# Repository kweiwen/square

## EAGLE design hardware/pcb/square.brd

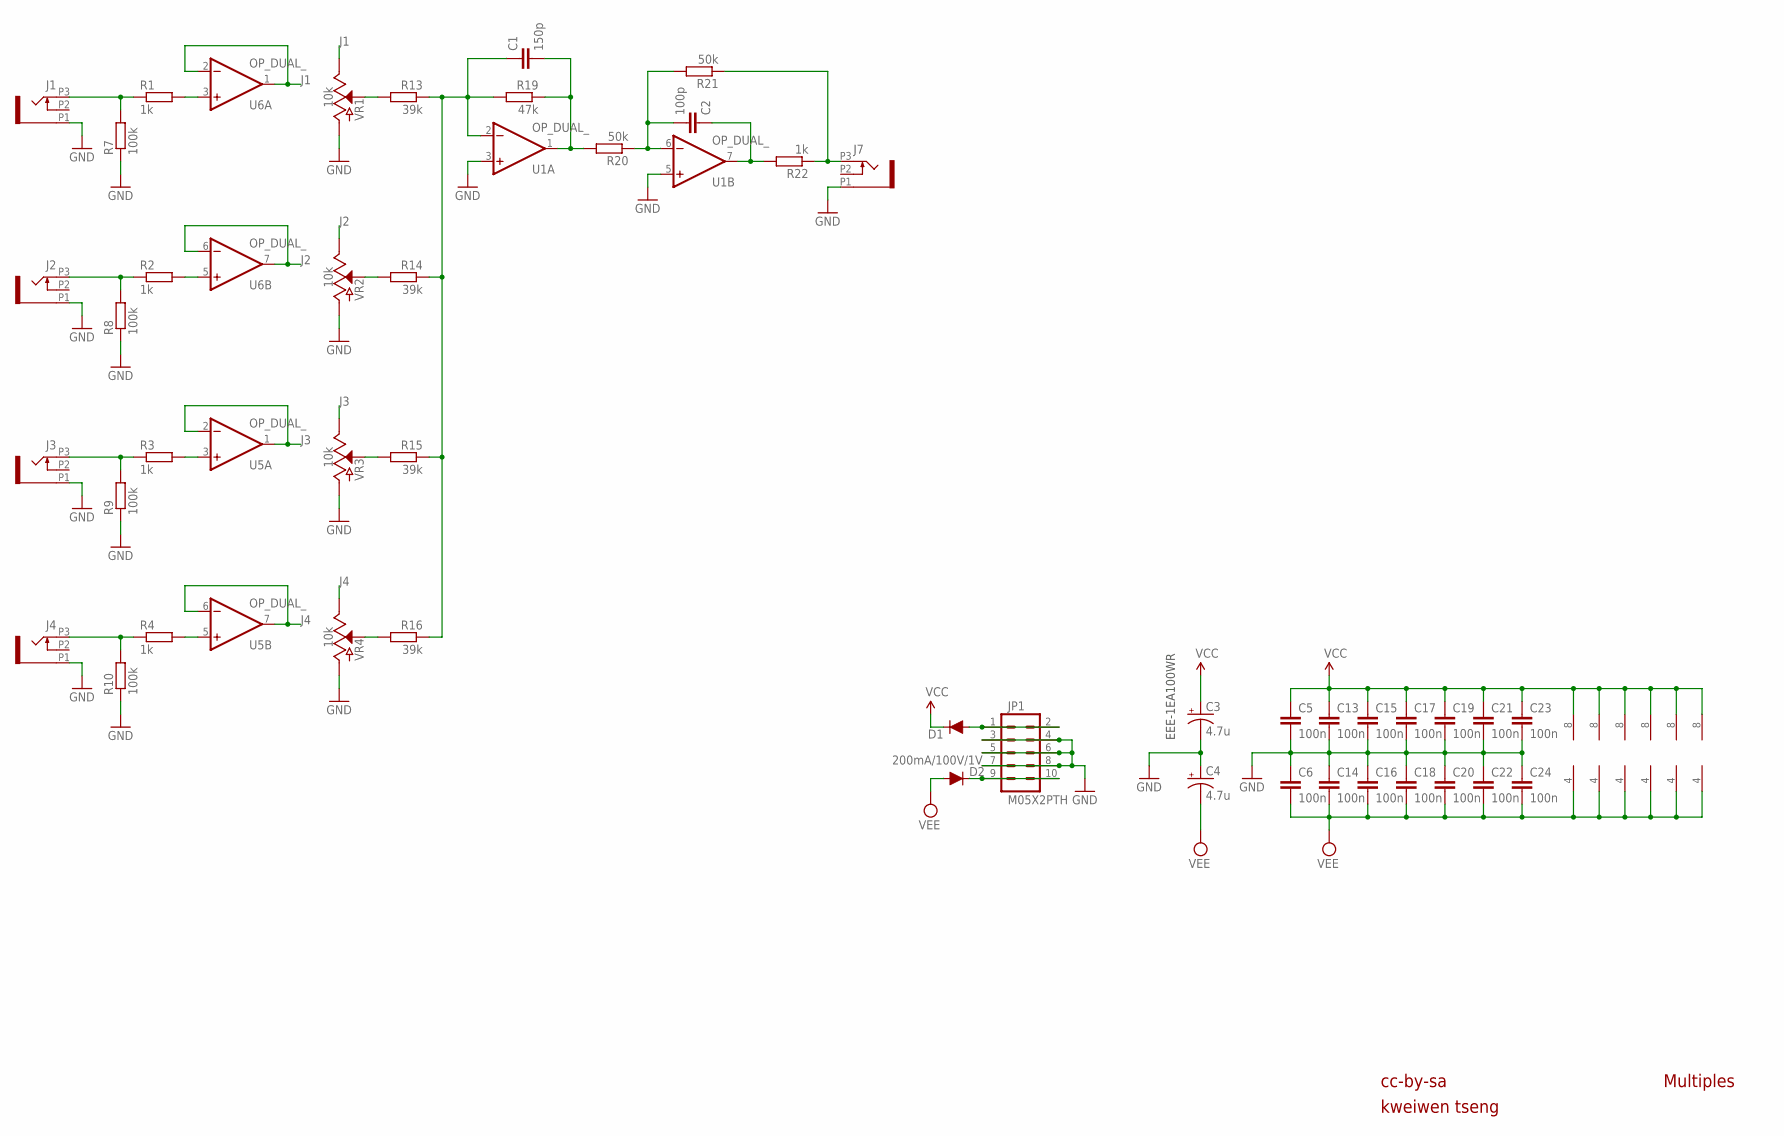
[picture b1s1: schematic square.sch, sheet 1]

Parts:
C1: 150p; C5B2.5
C2: 100p; C5B2.5
C3, C4: 4.7u; E2,5-6
C5, C6, C13, C14, C15, C16, C17, C18, C19, C20, C21, C22, C23, C24: 100n; C5B2.5
D1, D2: 200mA/100V/1V; DIODE-1N4148
J1, J2, J3, J4, J7: PJ301_THONKICONN6; WQP_PJ_301M6
JP1: M05X2PTH; AVR_ICSP
R1, R2, R3, R4, R22: 1k; VERTICAL_RESISTOR
R7, R8, R9, R10: 100k; VERTICAL_RESISTOR
R13, R14, R15, R16: 39k; VERTICAL_RESISTOR
R19: 47k; VERTICAL_RESISTOR
R20, R21: 50k; VERTICAL_RESISTOR
U1, U2, U3, U4, U5, U6: OP_DUAL_; DIL08
VR1, VR2, VR3, VR4: 10k; POT-PTH-ALPS-KIT

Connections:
GND: C3.-, C4.+, C5.2, C6.1, J1.P1 (1), J2.P1 (1), J3.P1 (1), J4.P1 (1), J7.P1 (1), JP1.3, JP1.4, JP1.5, JP1.6, JP1.7, JP1.8, R7.1, R8.1, R9.1, R10.1, U1.3 (+IN), U1.5 (+IN), VR1.P$1 (A), VR2.P$1 (A), VR3.P$1 (A), VR4.P$1 (A); also elsewhere on the board
GND1: C13.2, C14.1
GND2: C15.2, C16.1
GND3: C17.2, C18.1
GND4: C19.2, C20.1
GND5: C21.2, C22.1
GND6: C23.2, C24.1
J1: U6.1 (OUT), U6.2 (-IN), VR1.P$3 (E); also elsewhere on the board
J2: U6.6 (-IN), U6.7 (OUT), VR2.P$3 (E); also elsewhere on the board
J3: U5.1 (OUT), U5.2 (-IN), VR3.P$3 (E); also elsewhere on the board
J4: U5.6 (-IN), U5.7 (OUT), VR4.P$3 (E); also elsewhere on the board
unnamed: C1.1, R13.1, R14.1, R15.1, R16.1, R19.2, U1.2 (-IN)
unnamed: R13.2, VR1.P$2 (S)
unnamed: R16.2, VR4.P$2 (S)
unnamed: R1.2, U6.3 (+IN)
unnamed: R14.2, VR2.P$2 (S)
unnamed: D1.A, JP1.1, JP1.2
unnamed: R15.2, VR3.P$2 (S)
unnamed: C1.2, R19.1, R20.2, U1.1 (OUT)
unnamed: C2.2, R20.1, R21.2, U1.6 (-IN)
unnamed: C2.1, R22.2, U1.7 (OUT)
unnamed: J7.P3 (3), R21.1, R22.1
unnamed: R2.2, U6.5 (+IN)
unnamed: R3.2, U5.3 (+IN)
unnamed: D2.C, JP1.9, JP1.10
unnamed: J1.P3 (3), R1.1, R7.2
unnamed: J2.P3 (3), R2.1, R8.2
unnamed: J3.P3 (3), R3.1, R9.2
unnamed: J4.P3 (3), R4.1, R10.2
unnamed: R4.2, U5.5 (+IN)
VCC: C3.+, C5.1, C13.1, C15.1, C17.1, C19.1, C21.1, C23.1, D1.C, U1.8 (V+), U2.8 (V+), U3.8 (V+), U4.8 (V+), U5.8 (V+), U6.8 (V+)
VEE: C4.-, C6.2, C14.2, C16.2, C18.2, C20.2, C22.2, C24.2, D2.A, U1.4 (V-), U2.4 (V-), U3.4 (V-), U4.4 (V-), U5.4 (V-), U6.4 (V-)

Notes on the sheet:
cc-by-sa
kweiwen tseng
Multiples
EEE-1EA100WR

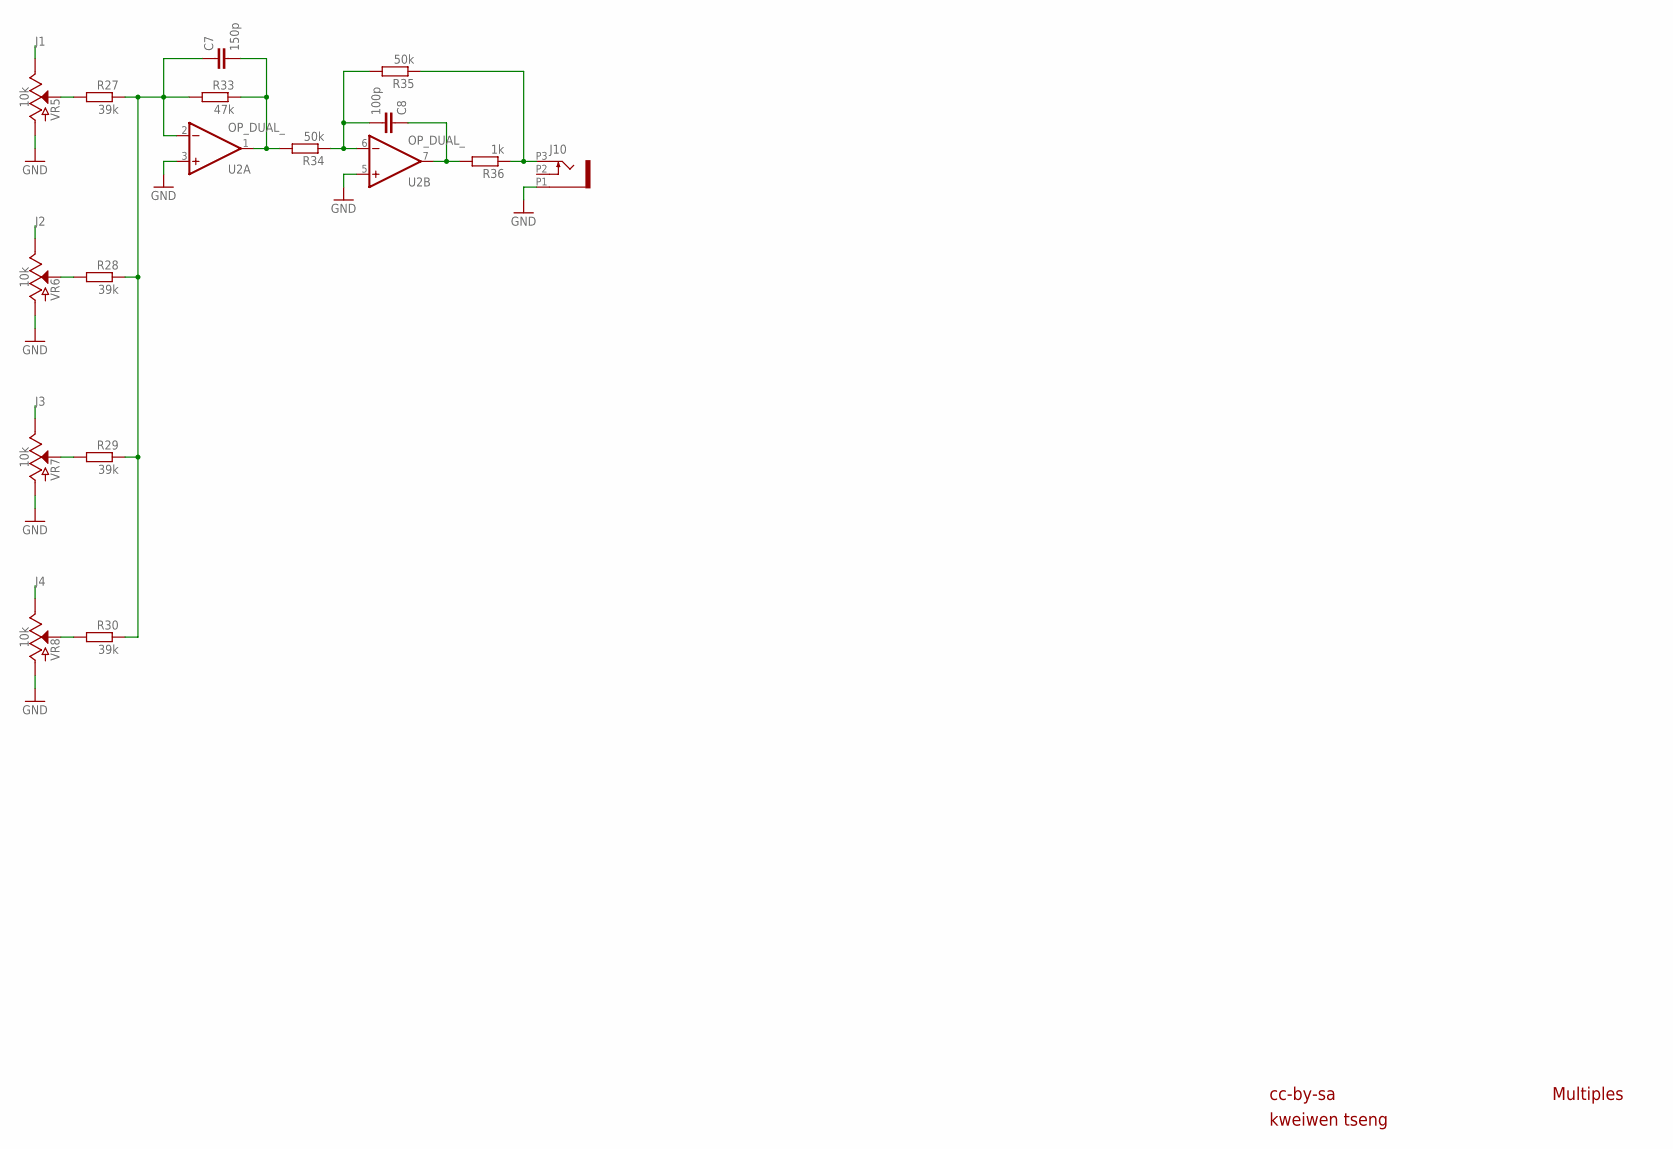
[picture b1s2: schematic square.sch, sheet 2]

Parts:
C7: 150p; C5B2.5
C8: 100p; C5B2.5
J10: PJ301_THONKICONN6; WQP_PJ_301M6
R27, R28, R29, R30: 39k; VERTICAL_RESISTOR
R33: 47k; VERTICAL_RESISTOR
R34, R35: 50k; VERTICAL_RESISTOR
R36: 1k; VERTICAL_RESISTOR
U2: OP_DUAL_; DIL08
VR5, VR6, VR7, VR8: 10k; POT-PTH-ALPS-KIT

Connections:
GND: J10.P1 (1), U2.3 (+IN), U2.5 (+IN), VR5.P$1 (A), VR6.P$1 (A), VR7.P$1 (A), VR8.P$1 (A); also elsewhere on the board
J1: VR5.P$3 (E); also elsewhere on the board
J2: VR6.P$3 (E); also elsewhere on the board
J3: VR7.P$3 (E); also elsewhere on the board
J4: VR8.P$3 (E); also elsewhere on the board
unnamed: R30.2, VR8.P$2 (S)
unnamed: C7.1, R27.1, R28.1, R29.1, R30.1, R33.2, U2.2 (-IN)
unnamed: C7.2, R33.1, R34.2, U2.1 (OUT)
unnamed: C8.2, R34.1, R35.2, U2.6 (-IN)
unnamed: J10.P3 (3), R35.1, R36.1
unnamed: C8.1, R36.2, U2.7 (OUT)
unnamed: R27.2, VR5.P$2 (S)
unnamed: R28.2, VR6.P$2 (S)
unnamed: R29.2, VR7.P$2 (S)

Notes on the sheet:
cc-by-sa
kweiwen tseng
Multiples

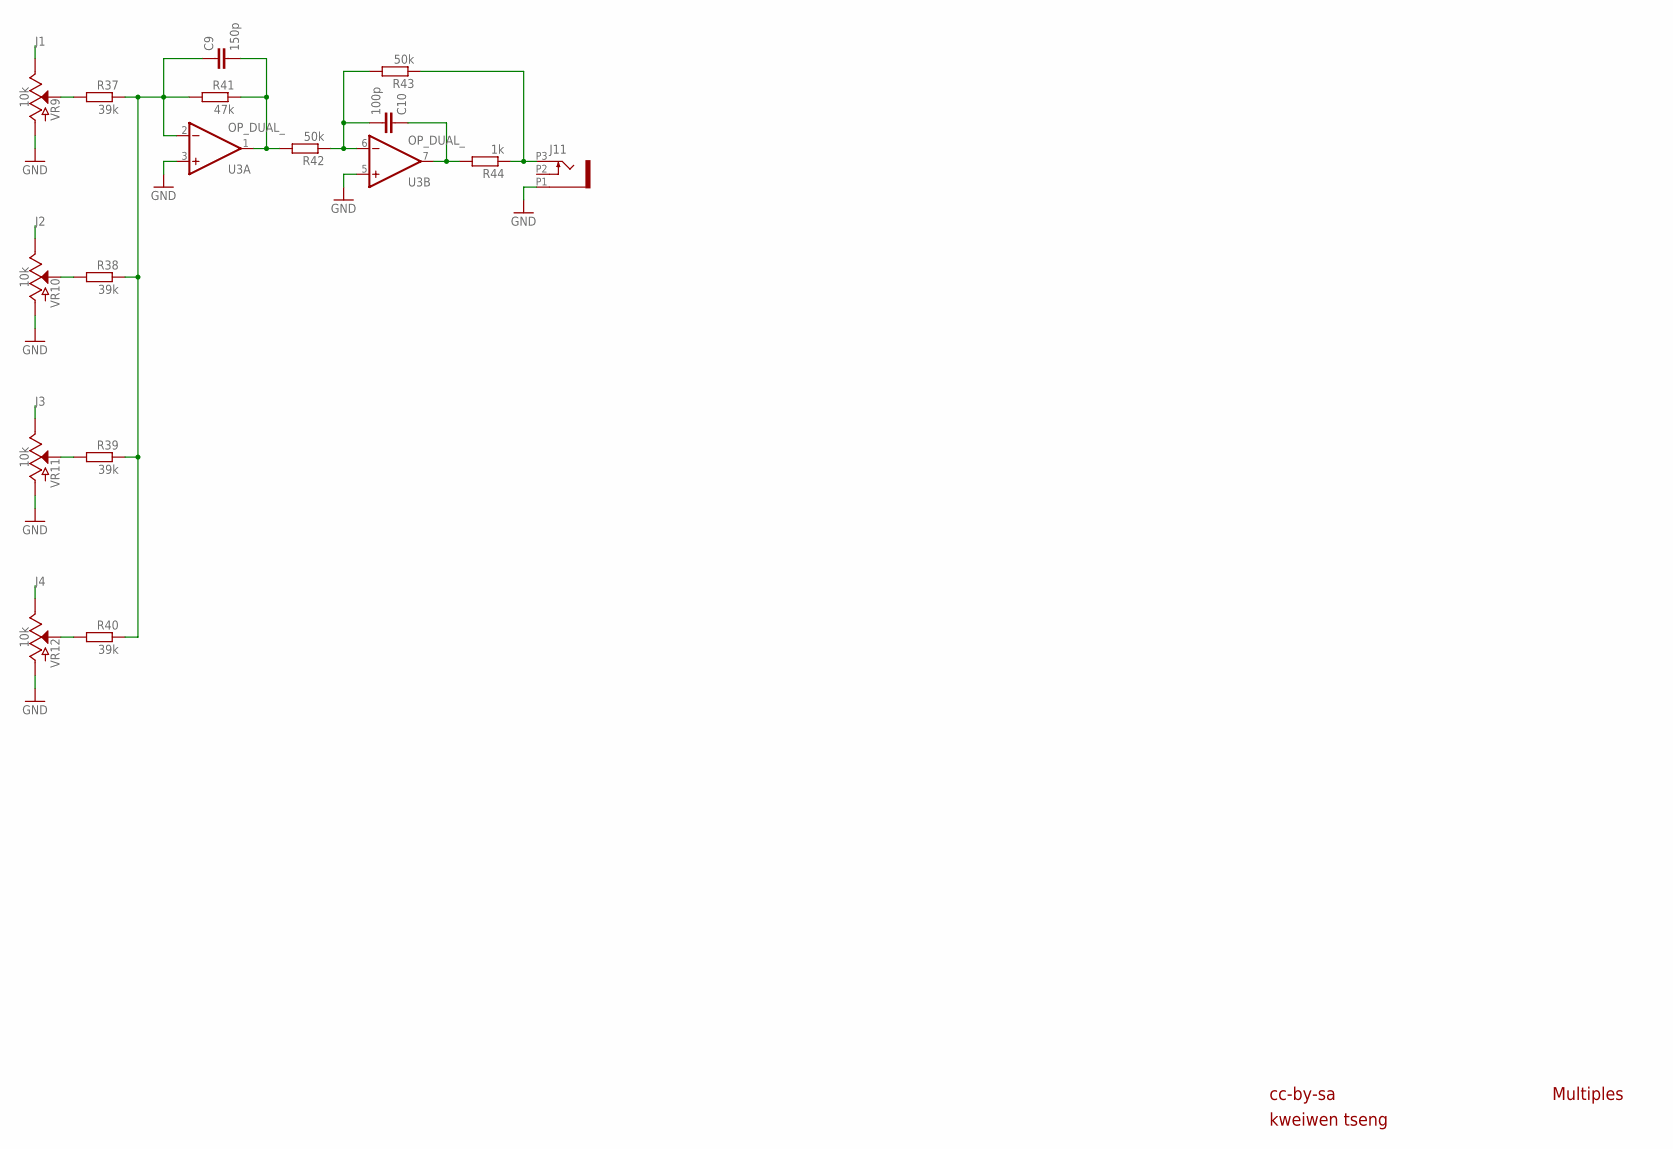
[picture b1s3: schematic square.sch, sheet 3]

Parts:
C9: 150p; C5B2.5
C10: 100p; C5B2.5
J11: PJ301_THONKICONN6; WQP_PJ_301M6
R37, R38, R39, R40: 39k; VERTICAL_RESISTOR
R41: 47k; VERTICAL_RESISTOR
R42, R43: 50k; VERTICAL_RESISTOR
R44: 1k; VERTICAL_RESISTOR
U3: OP_DUAL_; DIL08
VR9, VR10, VR11, VR12: 10k; POT-PTH-ALPS-KIT

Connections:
GND: J11.P1 (1), U3.3 (+IN), U3.5 (+IN), VR9.P$1 (A), VR10.P$1 (A), VR11.P$1 (A), VR12.P$1 (A); also elsewhere on the board
J1: VR9.P$3 (E); also elsewhere on the board
J2: VR10.P$3 (E); also elsewhere on the board
J3: VR11.P$3 (E); also elsewhere on the board
J4: VR12.P$3 (E); also elsewhere on the board
unnamed: R40.2, VR12.P$2 (S)
unnamed: C9.1, R37.1, R38.1, R39.1, R40.1, R41.2, U3.2 (-IN)
unnamed: C9.2, R41.1, R42.2, U3.1 (OUT)
unnamed: C10.2, R42.1, R43.2, U3.6 (-IN)
unnamed: J11.P3 (3), R43.1, R44.1
unnamed: C10.1, R44.2, U3.7 (OUT)
unnamed: R37.2, VR9.P$2 (S)
unnamed: R38.2, VR10.P$2 (S)
unnamed: R39.2, VR11.P$2 (S)

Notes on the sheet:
cc-by-sa
kweiwen tseng
Multiples

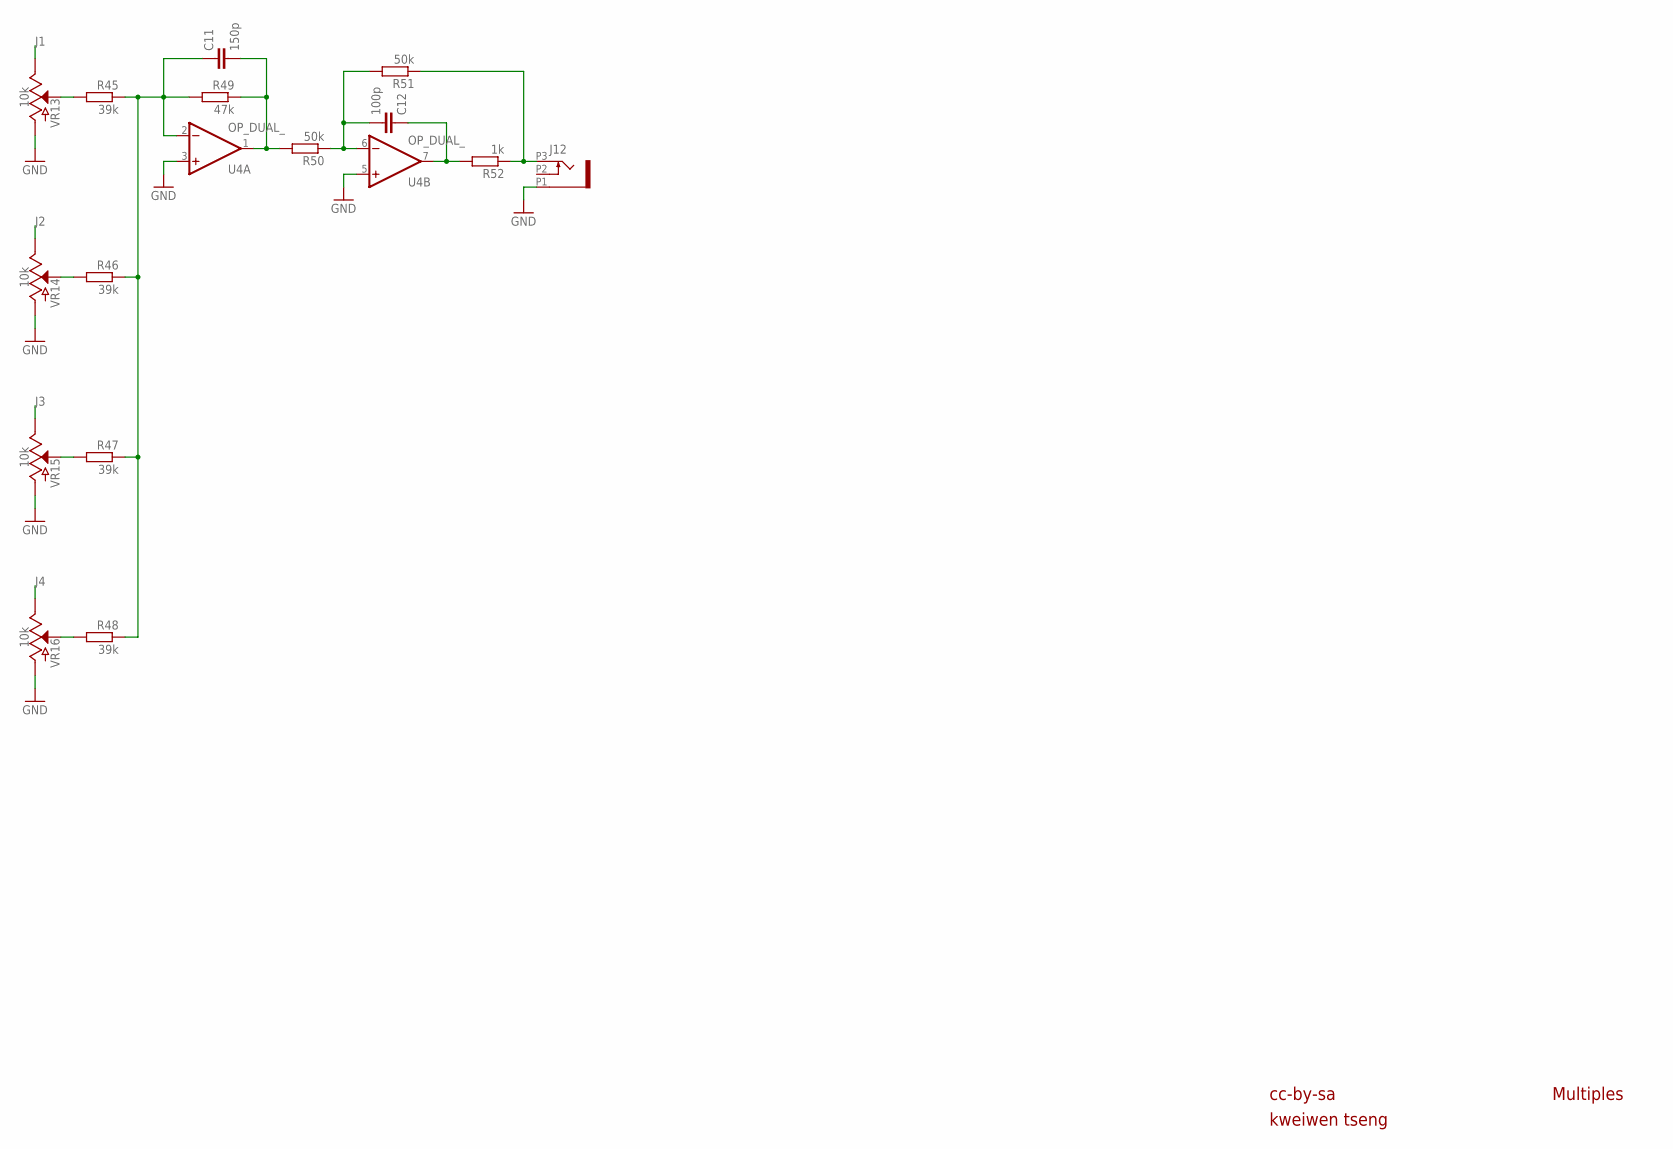
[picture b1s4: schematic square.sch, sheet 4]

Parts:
C11: 150p; C5B2.5
C12: 100p; C5B2.5
J12: PJ301_THONKICONN6; WQP_PJ_301M6
R45, R46, R47, R48: 39k; VERTICAL_RESISTOR
R49: 47k; VERTICAL_RESISTOR
R50, R51: 50k; VERTICAL_RESISTOR
R52: 1k; VERTICAL_RESISTOR
U4: OP_DUAL_; DIL08
VR13, VR14, VR15, VR16: 10k; POT-PTH-ALPS-KIT

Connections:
GND: J12.P1 (1), U4.3 (+IN), U4.5 (+IN), VR13.P$1 (A), VR14.P$1 (A), VR15.P$1 (A), VR16.P$1 (A); also elsewhere on the board
J1: VR13.P$3 (E); also elsewhere on the board
J2: VR14.P$3 (E); also elsewhere on the board
J3: VR15.P$3 (E); also elsewhere on the board
J4: VR16.P$3 (E); also elsewhere on the board
unnamed: R48.2, VR16.P$2 (S)
unnamed: C11.1, R45.1, R46.1, R47.1, R48.1, R49.2, U4.2 (-IN)
unnamed: C11.2, R49.1, R50.2, U4.1 (OUT)
unnamed: C12.2, R50.1, R51.2, U4.6 (-IN)
unnamed: J12.P3 (3), R51.1, R52.1
unnamed: C12.1, R52.2, U4.7 (OUT)
unnamed: R45.2, VR13.P$2 (S)
unnamed: R46.2, VR14.P$2 (S)
unnamed: R47.2, VR15.P$2 (S)

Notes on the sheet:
cc-by-sa
kweiwen tseng
Multiples

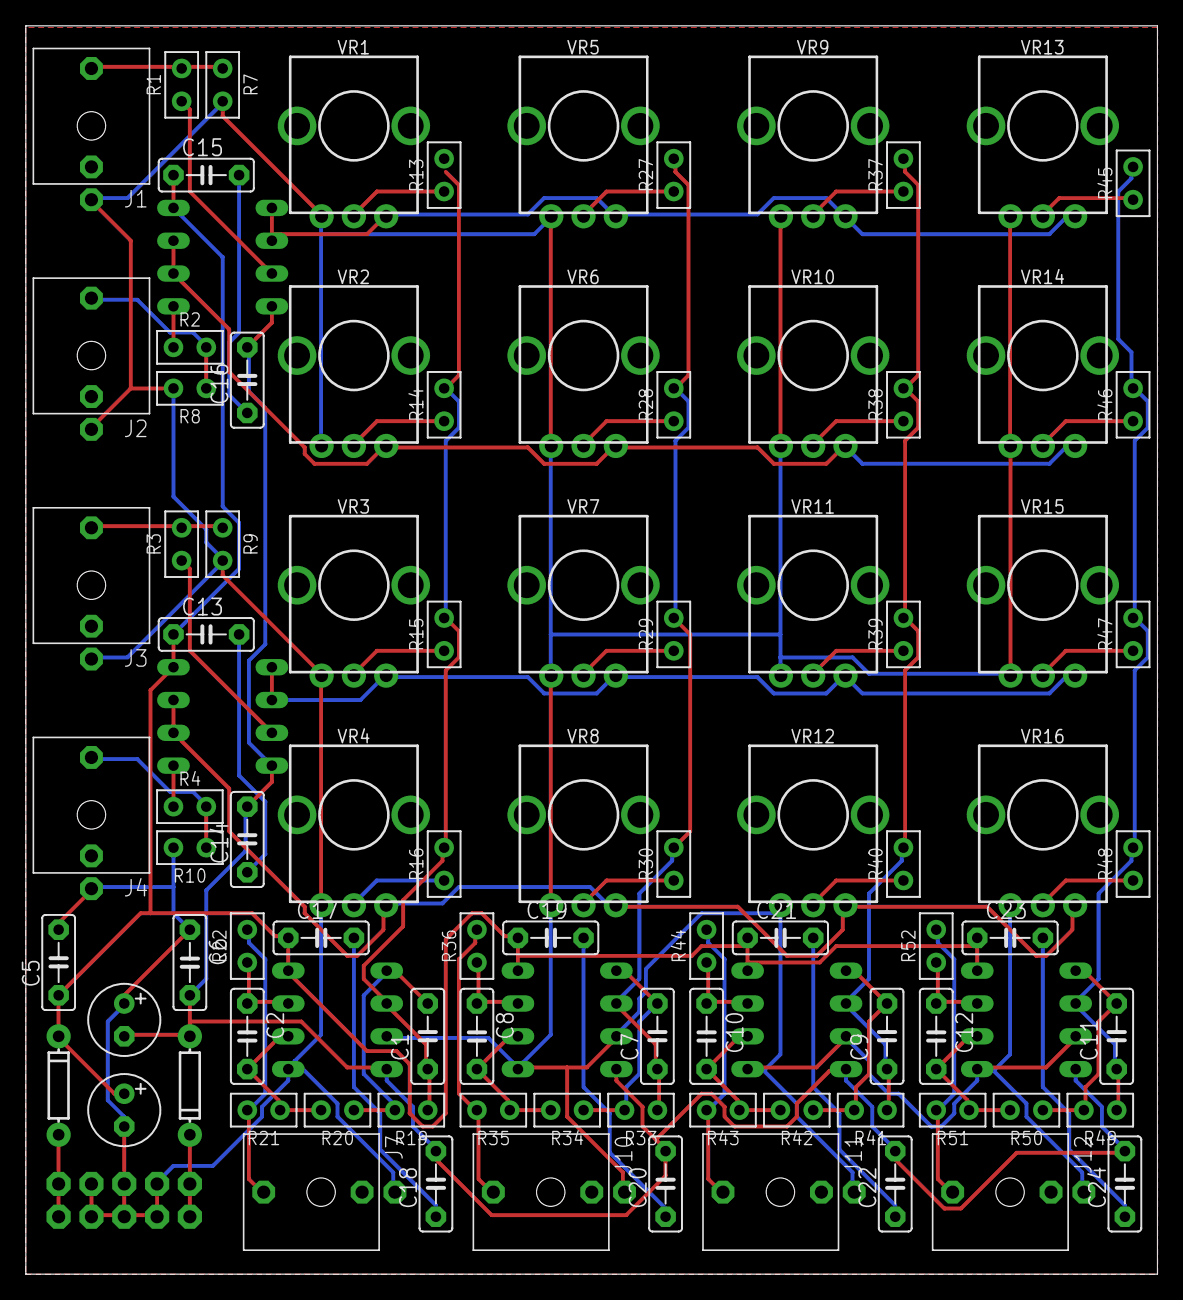
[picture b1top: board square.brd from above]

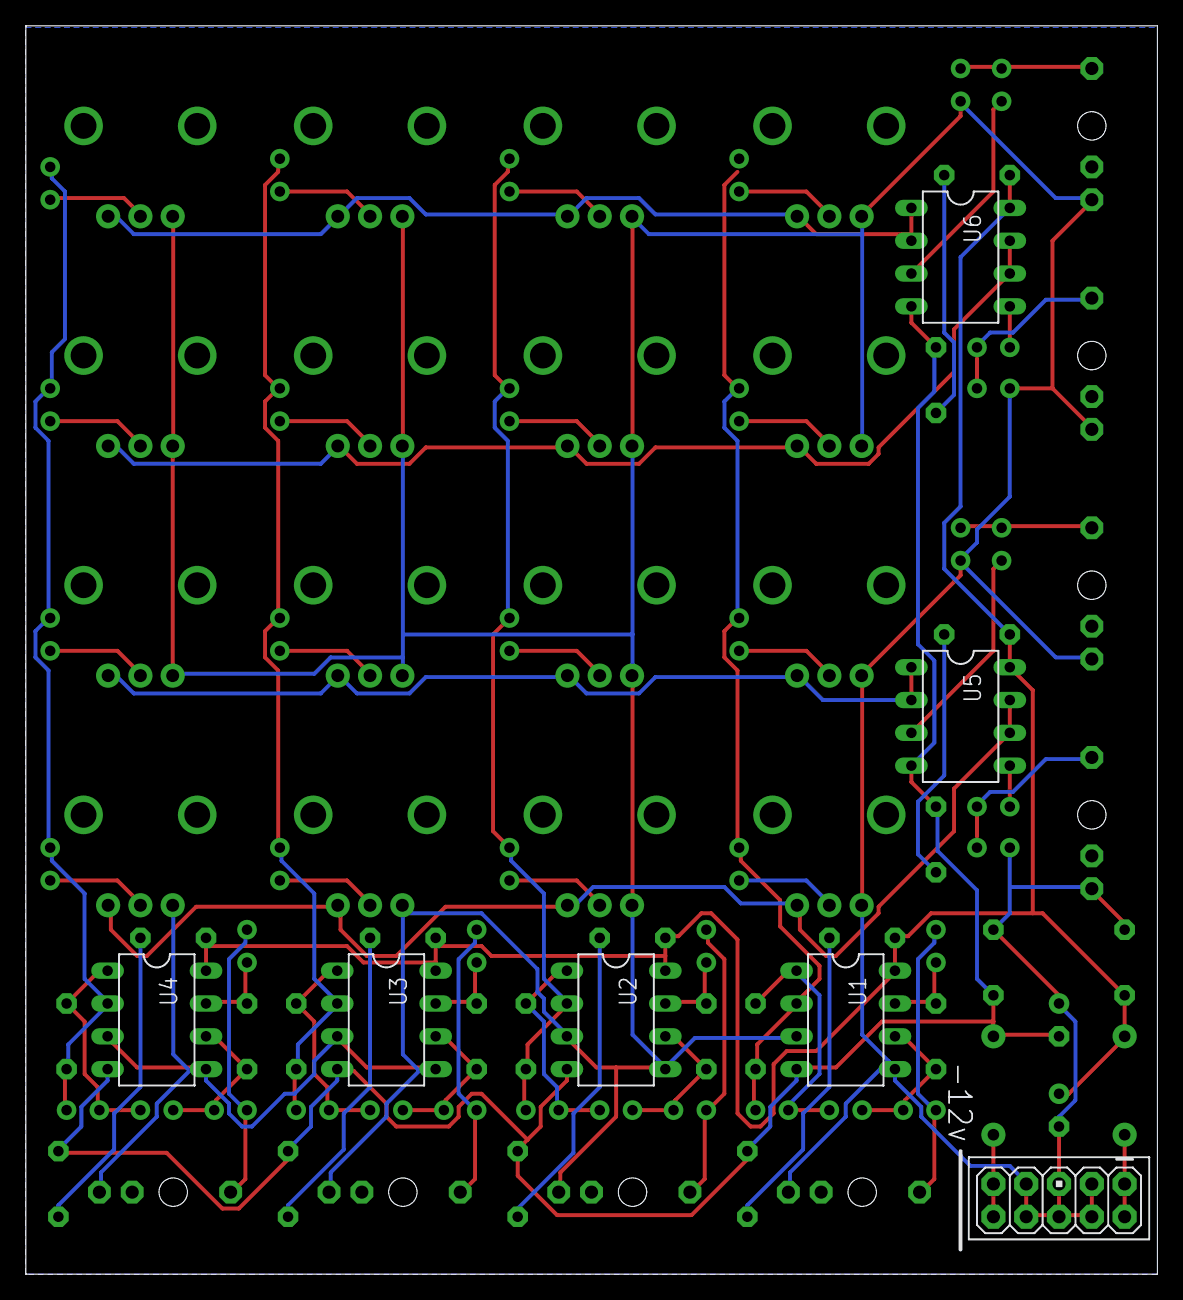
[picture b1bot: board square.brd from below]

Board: 2 copper layers, 87.6 x 96.6 mm, 97 parts (7 on the bottom side), 59 nets.

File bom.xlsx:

Square
Qty | Value | Device | Package | Parts | Description
14 | 100n | C5/2.5 | C5B2.5 | C5, C6, C13, C14, C15, C16, C17, C18, C19, C20, C21, C22, C23, C24 | CAPACITOR
4 | 100p | C5/2.5 | C5B2.5 | C2, C8, C10, C12 | CAPACITOR
4 | 150p | C5/2.5 | C5B2.5 | C1, C7, C9, C11 | CAPACITOR
2 | 4.7u | CPOL-USE2.5-6 | E2,5-6 | C3, C4 | POLARIZED CAPACITOR, American symbol
2 | 1N4001 | DIODE | DIODE | D1, D2 | Protection Diode
1 | M05X2PTH | M05X2PTH | AVR_ICSP | JP1 | Header 5x2
8 | PJ301_THONKICONN6 | PJ301_THONKICONN6 | WQP_PJ_301M6 | J1, J2, J3, J4, J7, J10, J11, J12
16 | 10k | POTENTIOMETER-PTH-9MM-1/20W-20%-KIT | POT-PTH-ALPS-KIT | VR1, VR2, VR3, VR4, VR5, VR6, VR7, VR8, VR9, VR10, VR11, VR12, VR13, VR14, VR15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 | Potentiometer (Pot)
4 | 100k | RESISTOR*VERTICAL | VERTICAL_RESISTOR | R7, R8, R9, R10 | Standard resistor, various versions
8 | 1k | RESISTOR*VERTICAL | VERTICAL_RESISTOR | R1, R2, R3, R4, R22, R36, R44, R52 | Standard resistor, various versions
16 | 39k | RESISTOR*VERTICAL | VERTICAL_RESISTOR | R13, R14, R15, R16, R27, R28, R29, R30, R37, R38, R39, R40, R45, R46, R47, R48 | Standard resistor, various versions
4 | 47k | RESISTOR*VERTICAL | VERTICAL_RESISTOR | R19, R33, R41, R49 | Standard resistor, various versions
8 | 50k | RESISTOR*VERTICAL | VERTICAL_RESISTOR | R20, R21, R34, R35, R42, R43, R50, R51 | Standard resistor, various versions
6 | TL072 | TL072 | DIL08 | U1, U2, U3, U4, U5, U6 | Generic Dual Op Amp

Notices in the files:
parts and their libraries:
SparkFun-DiscreteSemi: Licensing: Creative Commons ShareAlike 4.0 International - https://creativecommons.org/licenses/by-sa/4.0
